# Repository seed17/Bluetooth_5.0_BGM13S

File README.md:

# Bluetooth_5.0_BGM13S (non-maintaned)
Bluetooth 5.1 technology (5.0 chip) BGM13S Module pcb

Me and my parthner decided to order the latest bluetooth [28 May 2019], bluetooth 5.1 chip.
Here is a video of the chip we ordered:

https://www.youtube.com/watch?v=CzmL0PJlgWI

We made a footprint for the chip, and a schematic, using KiCad. 

The libraries i used, along with the other, custom libraries i use in KiCad, can be found here: https://github.com/Basilisvirus/VirusCad_Lib.git

We designed a pcb with all the neccesary pins and connections to make it a module/dev board.

The antenna is the only part we have not tested yet. We are unsure of its proper functionality, since it needs to be at a proper length and loop distance

Enjoy.

Questions? issues? email me: basilisvirus@hotmail.com

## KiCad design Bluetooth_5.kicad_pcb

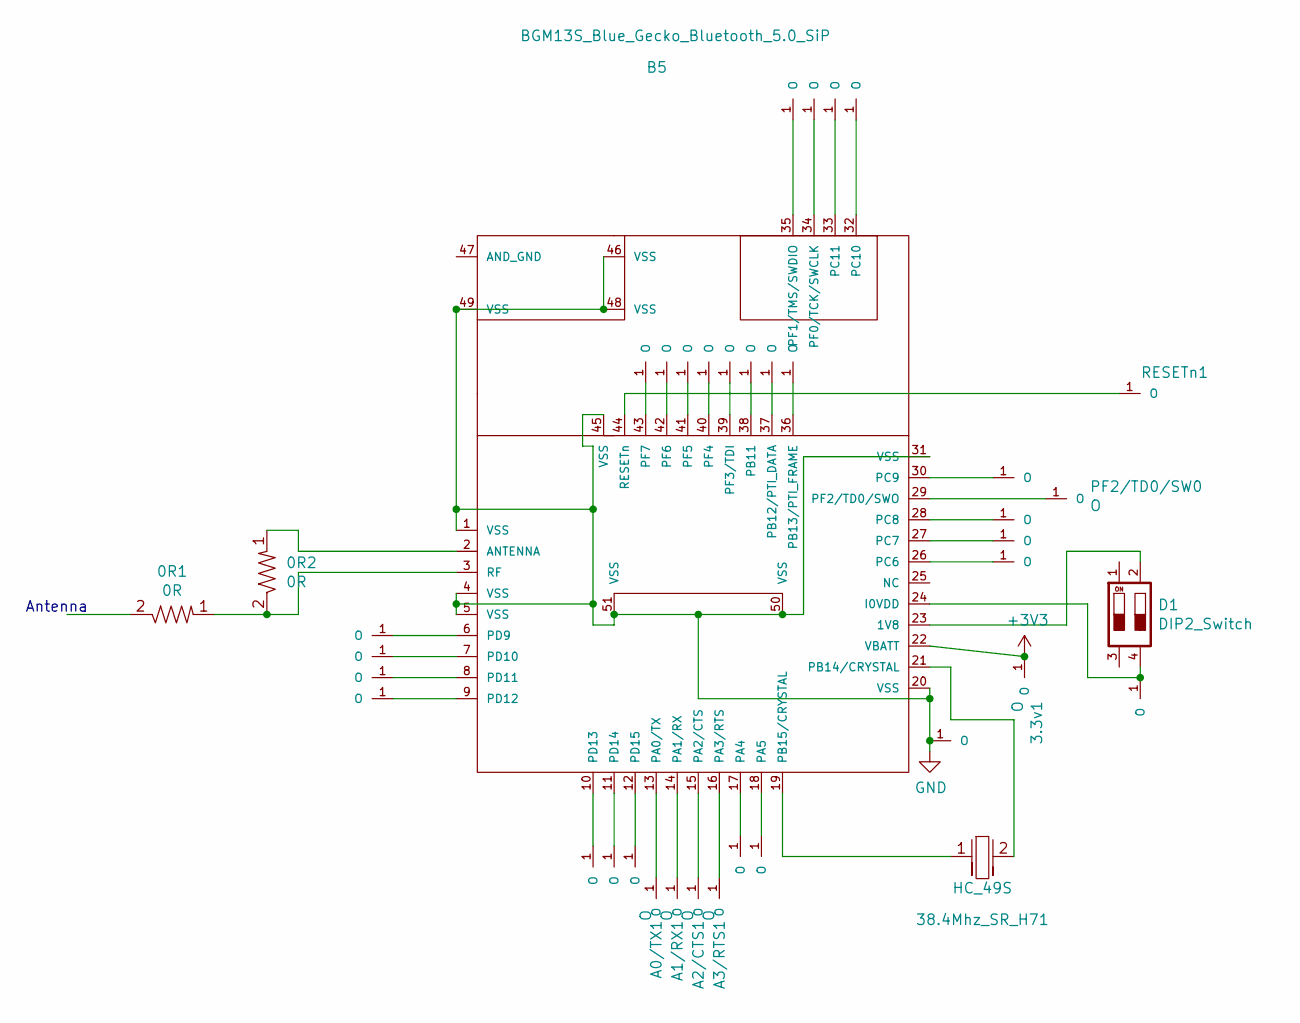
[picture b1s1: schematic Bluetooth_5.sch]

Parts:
0R1, 0R2: 0R; 1206_res_smd
3.3v1: O; Ο
38.4Mhz_SR_H71: HC_49S
A0/TX1, A1/RX1, A2/CTS1, A3/RTS1, A4, A5: O; Ο
B5: BGM13S_Blue_Gecko_Bluetooth_5.0_SiP; BGM13S Blue Gecko Bluetooth 5.0 SiP
B11, B12/PTI_DATA1, B13/PTI_FRAME1: O; Ο
C6, C7, C8, C9, C10, C11: O; Ο
D1: DIP2_Switch
D9, D10, D11, D12, D13, D14, D15: O; Ο
F1/TMS/SWDI0, F3/TDI1, F4, F5, F6, F7: O; Ο
GND1: O; Ο
IOVDD1: O; Ο
PF0/TCK/SWCLK1, PF2/TD0/SW0: O; Ο
RESETn1: GPIO; Ο

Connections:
+3V3: 3.3v1.1, B5.22 (VBATT)
GND: B5.1 (VSS), B5.4 (VSS), B5.5 (VSS), B5.20 (VSS), B5.31 (VSS), B5.45 (VSS), B5.46 (VSS), B5.48 (VSS), B5.49 (VSS), B5.50 (VSS), B5.51 (VSS), GND1.1
unnamed: 0R1.1, 0R2.2, B5.3 (RF)
unnamed: 0R2.1, B5.2 (ANTENNA)
unnamed: 38.4Mhz_SR_H71.1, B5.19 (PB15/CRYSTAL)
unnamed: 38.4Mhz_SR_H71.2, B5.21 (PB14/CRYSTAL)
unnamed: A0/TX1.1, B5.13 (PA0/TX)
unnamed: A1/RX1.1, B5.14 (PA1/RX)
unnamed: A2/CTS1.1, B5.15 (PA2/CTS)
unnamed: A3/RTS1.1, B5.16 (PA3/RTS)
unnamed: A4.1, B5.17 (PA4)
unnamed: A5.1, B5.18 (PA5)
unnamed: B5.6 (PD9), D9.1
unnamed: B5.7 (PD10), D10.1
unnamed: B5.8 (PD11), D11.1
unnamed: B5.9 (PD12), D12.1
unnamed: B5.10 (PD13), D13.1
unnamed: B5.11 (PD14), D14.1
unnamed: B5.12 (PD15), D15.1
unnamed: B5.23 (1V8), D1.2
unnamed: B5.24 (I0VDD), D1.4, IOVDD1.1
unnamed: B5.26 (PC6), C6.1
unnamed: B5.27 (PC7), C7.1
unnamed: B5.28 (PC8), C8.1
unnamed: B5.29 (PF2/TD0/SWO), PF2/TD0/SW0.1
unnamed: B5.30 (PC9), C9.1
unnamed: B5.32 (PC10), C10.1
unnamed: B5.33 (PC11), C11.1
unnamed: B5.34 (PF0/TCK/SWCLK), PF0/TCK/SWCLK1.1
unnamed: B5.35 (PF1/TMS/SWDIO), F1/TMS/SWDI0.1
unnamed: B5.39 (PF3/TDI), F3/TDI1.1
unnamed: B5.40 (PF4), F4.1
unnamed: B5.41 (PF5), F5.1
unnamed: B5.42 (PF6), F6.1
unnamed: B5.43 (PF7), F7.1
unnamed: B5.44 (RESETn), RESETn1.1
unnamed: B5.38 (PB11), B11.1
unnamed: B5.37 (PB12/PTI_DATA), B12/PTI_DATA1.1
unnamed: B5.36 (PB13/PTI_FRAME), B13/PTI_FRAME1.1

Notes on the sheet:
Antenna

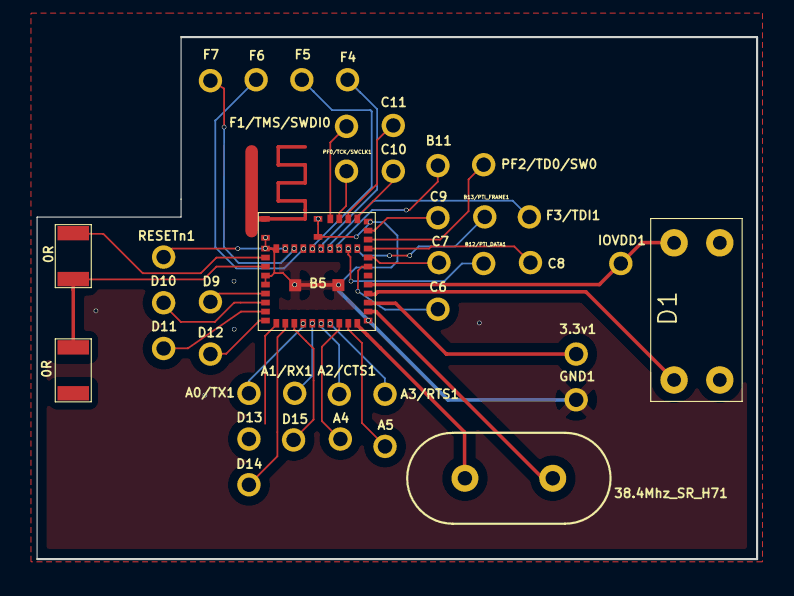
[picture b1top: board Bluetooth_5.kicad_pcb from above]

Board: 2 copper layers, 40.0 x 29.0 mm, 39 parts (0 on the bottom side), 39 nets.

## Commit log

2019-05-28 added bluetooth
2019-05-28 changed pcb ground plane, made corrections
2019-06-12 added datasheet and oscillator Crystal Hz
